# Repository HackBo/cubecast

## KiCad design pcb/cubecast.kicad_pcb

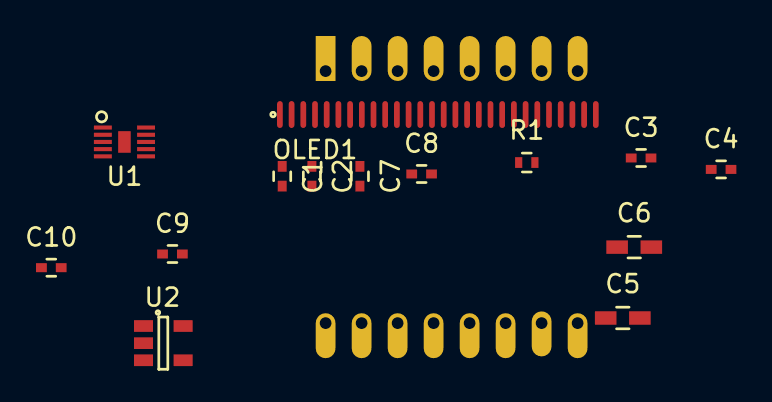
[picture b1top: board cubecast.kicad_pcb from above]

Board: 2 copper layers, 15 parts (1 on the bottom side), 10 nets, no tracks yet.

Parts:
C1, C2: 1.0uF; C_0402
C3, C4: 2.2uF; C_0402
C5, C6: 10uF; C_0603_HandSoldering
C7, C8, C9, C10: 0.1uF; C_0402
OLED1: OLED_0.66_inch_64x48
R1: 390k; R_0402
U1: bq24040; R-PWSON-N10
U2: tps62200; SOT-23-5
U3: ESP-07v2

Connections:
+3V3: C6.1, C7.1, C8.1, C9.1, C10.1, OLED1.6, OLED1.8, U2.4, U3.8
/VOUT: C5.1, U1.10, U2.1, U2.3
GND: C3.2, C4.2, C5.2, C6.2, C7.2, C8.2, C9.2, C10.2, OLED1.1, OLED1.7, OLED1.27, OLED1.28, R1.2, U2.2, U3.9
unnamed: C1.1, OLED1.2
unnamed: C1.2, OLED1.3
unnamed: C2.1, OLED1.4
unnamed: C2.2, OLED1.5
unnamed: C3.1, OLED1.26
unnamed: C4.1, OLED1.25
unnamed: OLED1.24, R1.1

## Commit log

2015-08-08 cubecast started
2015-08-09 PCB started
2015-08-10 initial placement
2015-08-11 footprint for charger
